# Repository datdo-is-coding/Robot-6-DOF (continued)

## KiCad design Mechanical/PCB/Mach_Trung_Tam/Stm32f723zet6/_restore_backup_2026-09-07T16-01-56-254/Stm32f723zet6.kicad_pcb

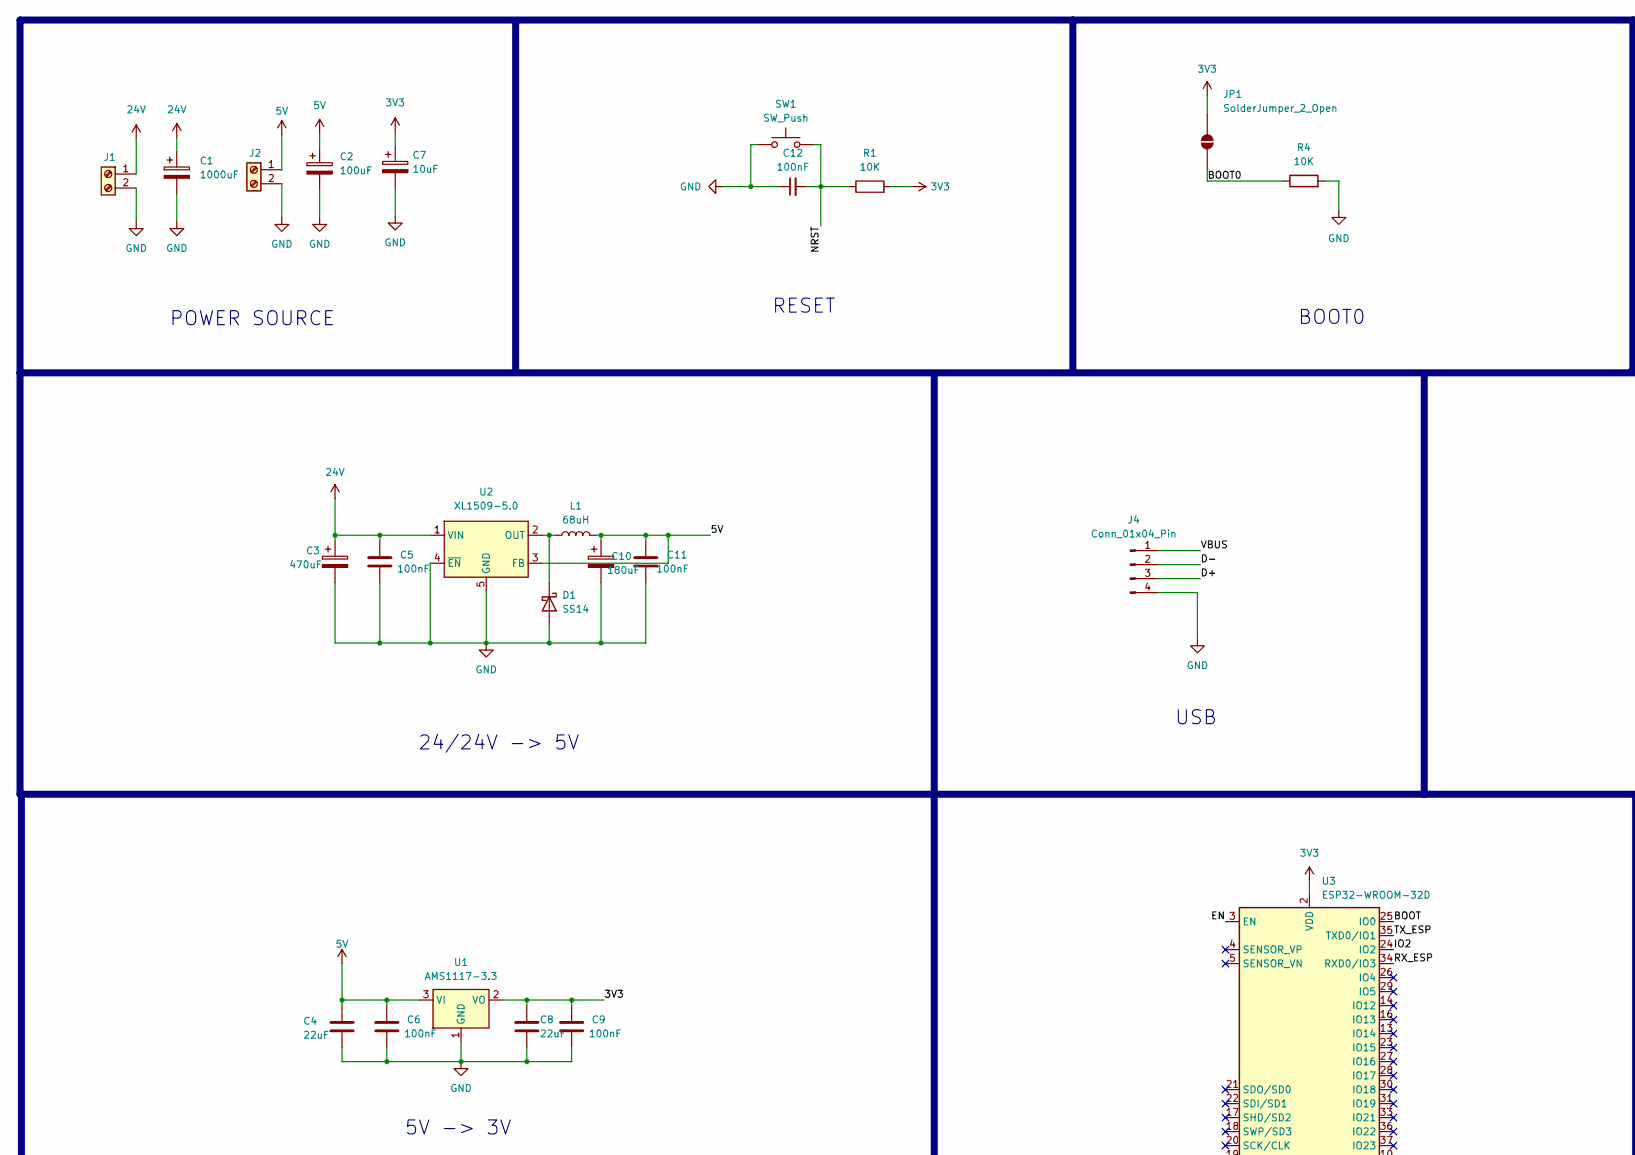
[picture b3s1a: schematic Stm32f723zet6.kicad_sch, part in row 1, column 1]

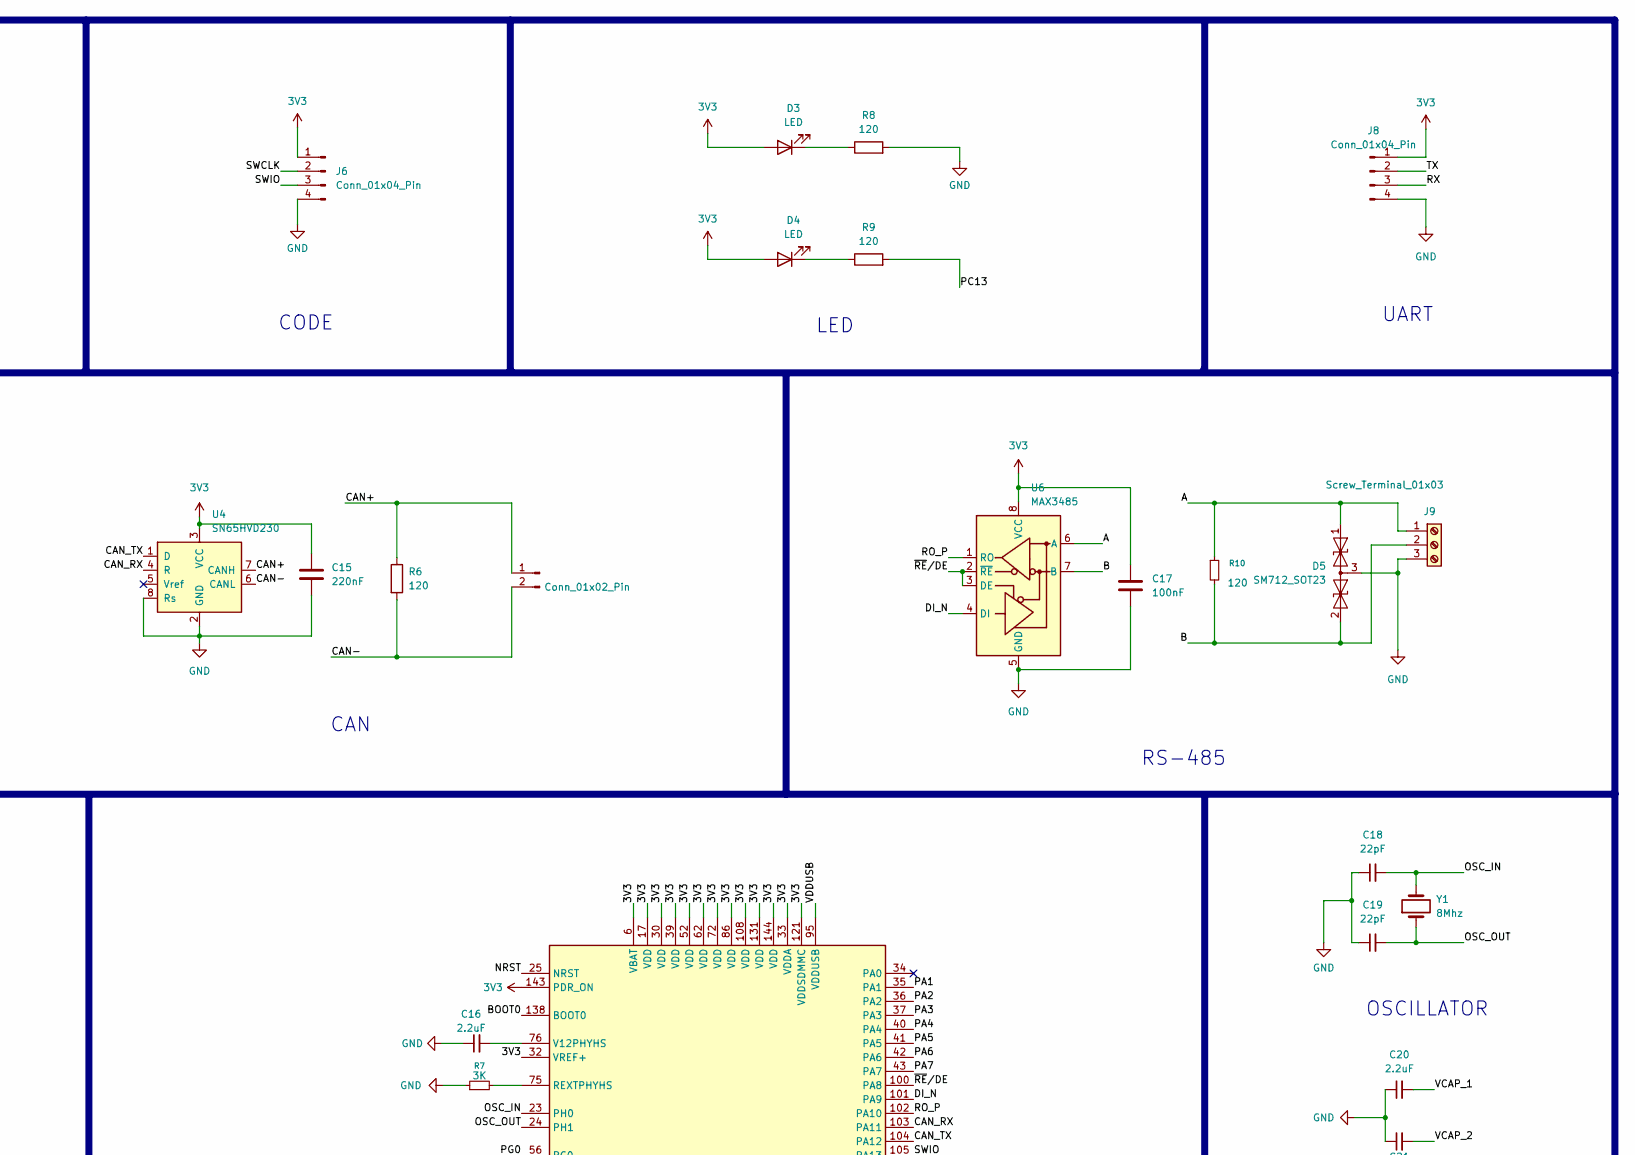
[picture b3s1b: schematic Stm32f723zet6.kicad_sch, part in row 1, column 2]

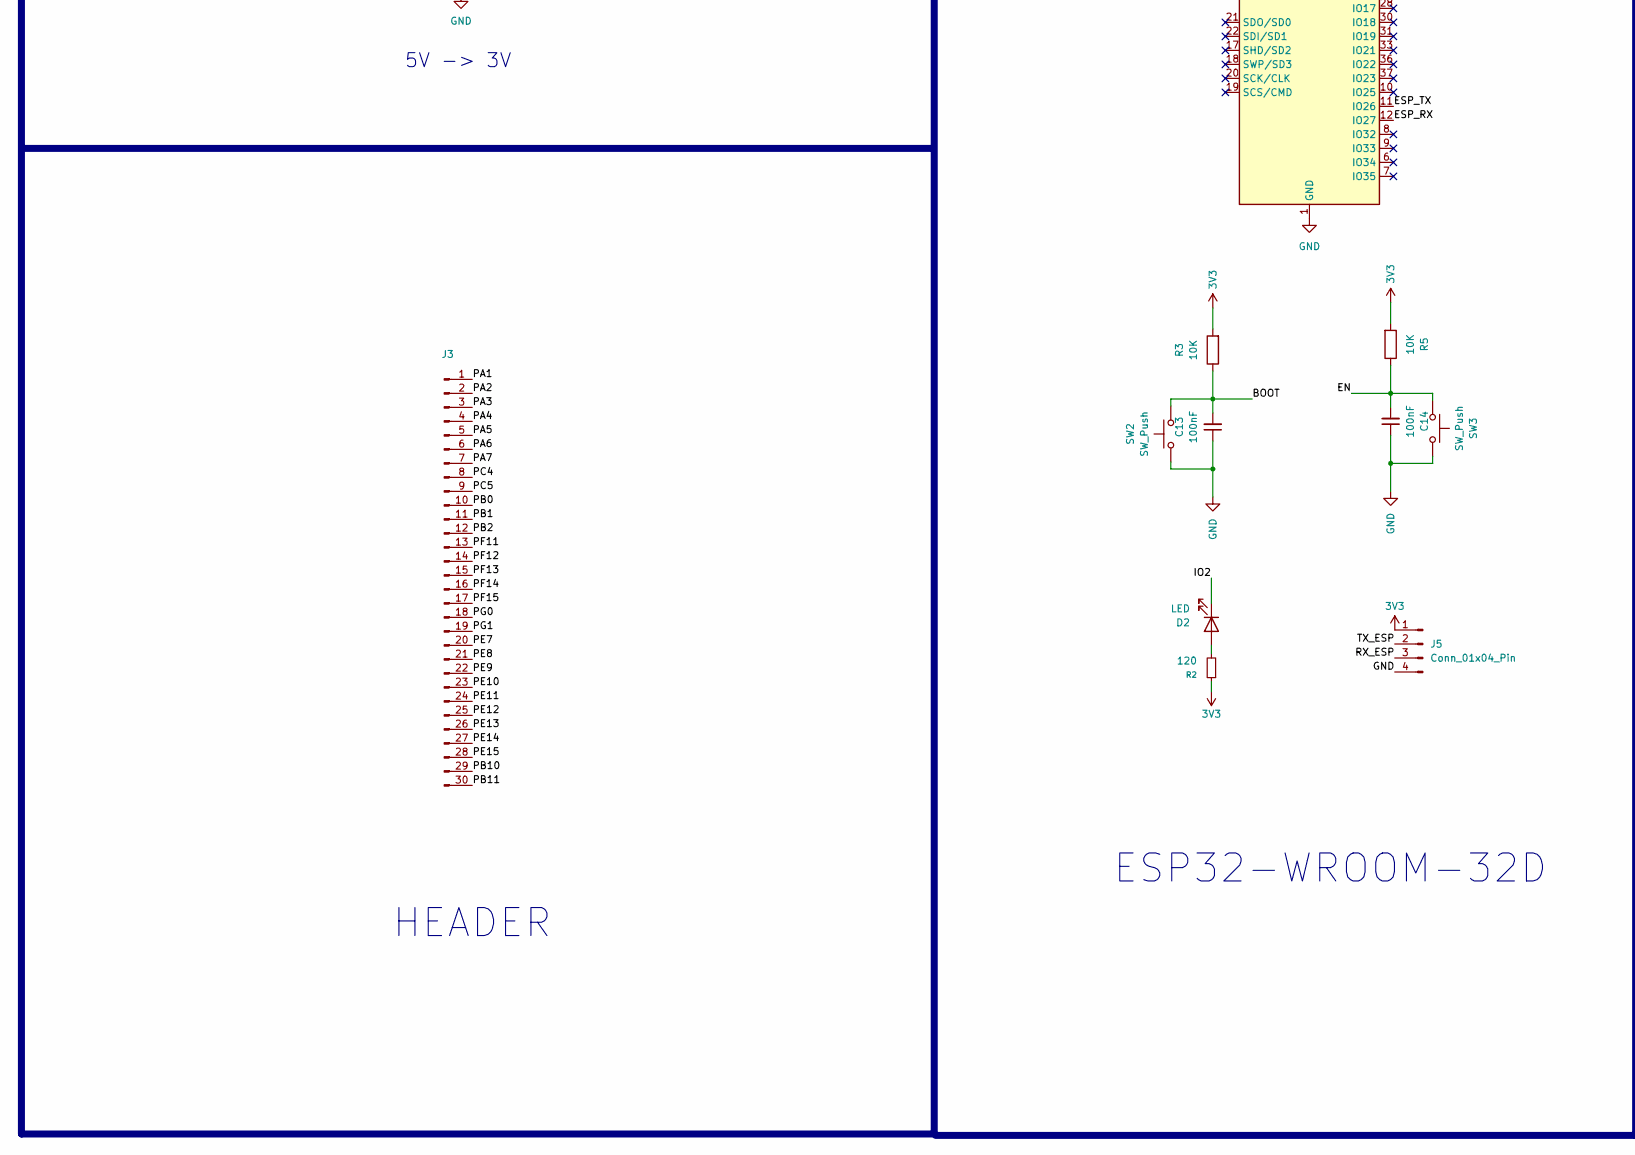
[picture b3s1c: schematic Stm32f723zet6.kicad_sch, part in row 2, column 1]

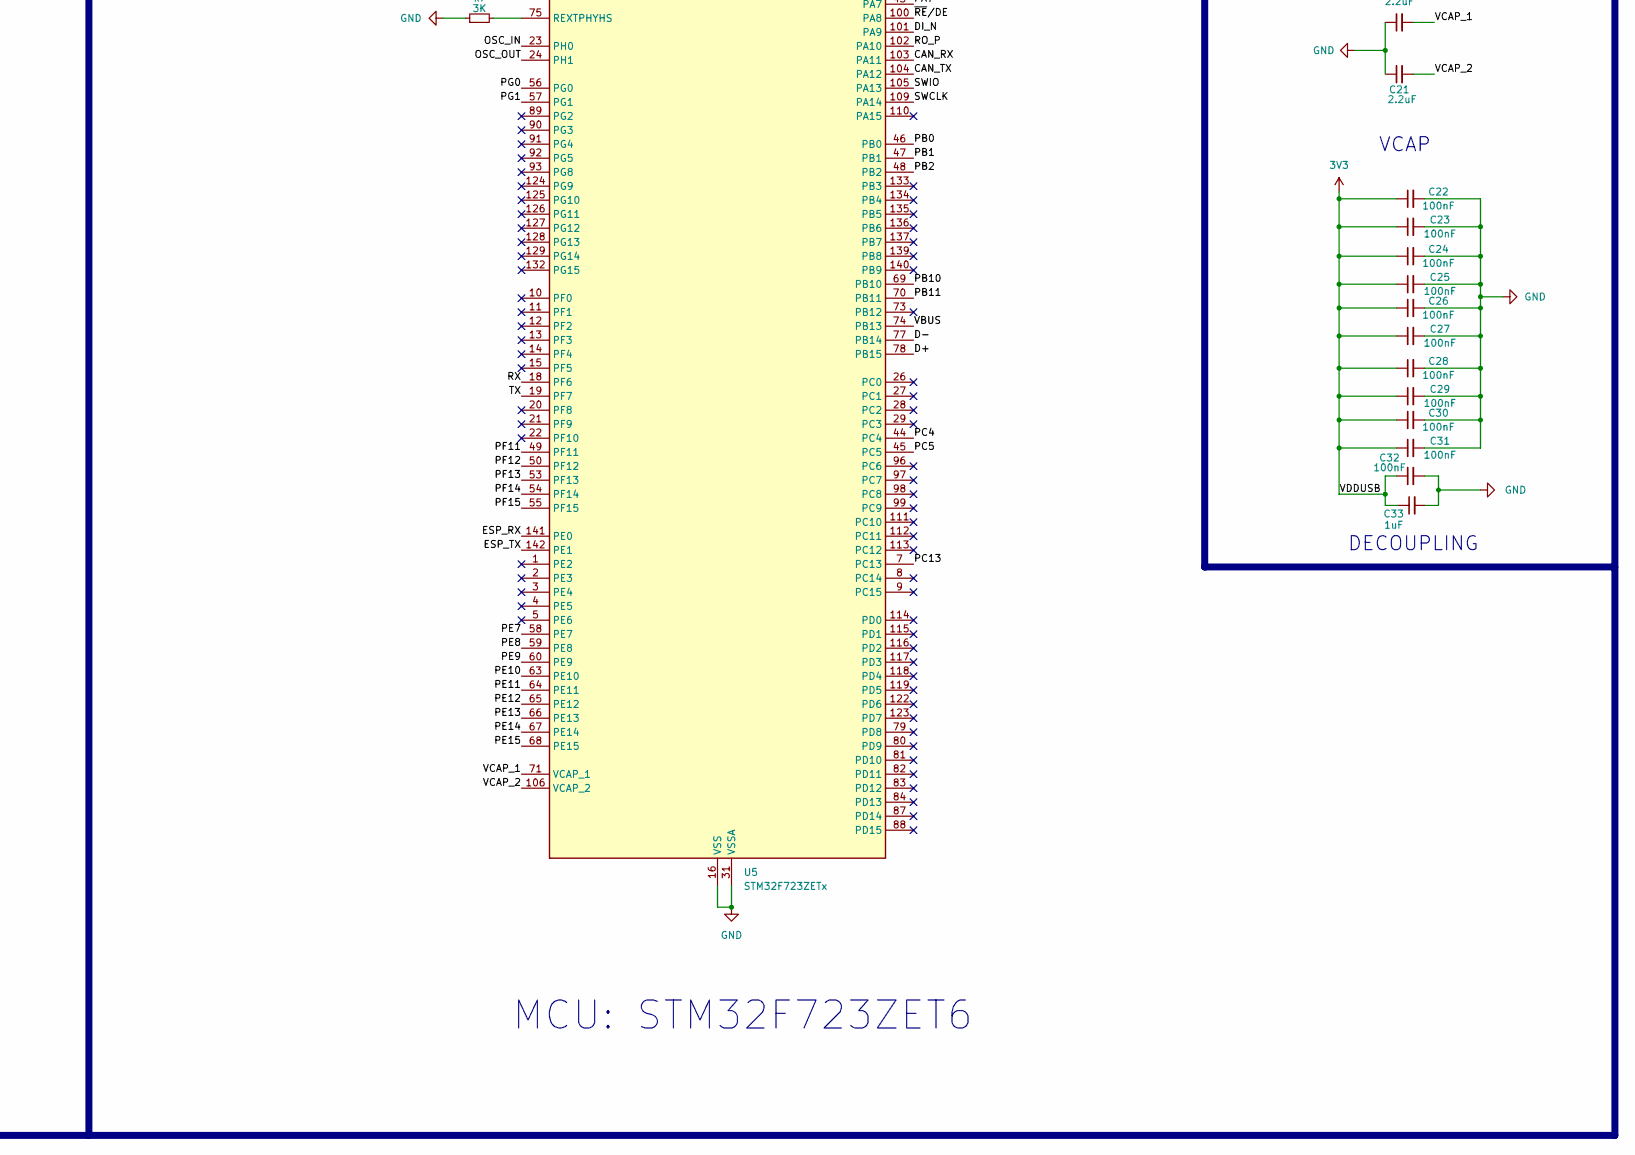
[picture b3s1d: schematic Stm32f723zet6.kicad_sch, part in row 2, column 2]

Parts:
C1: 1000uF; CP_Elec_10x10.5
C2: 100uF; CP_Elec_6.3x5.4
C3: 470uF; CP_Elec_8x10.5
C4, C8: 22uF; C_0805_2012Metric_Pad1.18x1.45mm_HandSolder
C5, C6, C9, C11, C12, C13, C14, C17, C22, C23, C24, C25, C26, C27, C28, C29, C30, C31, C32: 100nF; C_0805_2012Metric_Pad1.18x1.45mm_HandSolder
C7: 10uF; CP_Elec_4x5.4
C10: 180uF; CP_Elec_8x10
C15: 220nF; C_0805_2012Metric_Pad1.18x1.45mm_HandSolder
C16, C20, C21: 2.2uF; C_0805_2012Metric_Pad1.18x1.45mm_HandSolder
C18, C19: 22pF; C_0805_2012Metric_Pad1.18x1.45mm_HandSolder
C33: 1uF; C_0805_2012Metric_Pad1.18x1.45mm_HandSolder
D1: SS14; D_SMA
D2, D3, D4: LED; LED_0805_2012Metric_Pad1.15x1.40mm_HandSolder
D5: SM712_SOT23; SOT-23
J1: Screw_Terminal_01x02; TerminalBlock_Phoenix_MKDS-1,5-2-5.08_1x02_P5.08mm_Horizont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
J2: Screw_Terminal_01x02; TerminalBlock_Phoenix_PT-1,5-2-3.5-H_1x02_P3.50mm_Horizontal
J3: Conn_01x30_Pin; PinHeader_1x30_P2.54mm_Vertical
J4, J5, J6, J8: Conn_01x04_Pin; PinHeader_1x04_P2.54mm_Vertical
J7: Conn_01x02_Pin; PinHeader_1x02_P2.54mm_Vertical
J9: Screw_Terminal_01x03; TerminalBlock_Phoenix_PT-1,5-3-3.5-H_1x03_P3.50mm_Horizontal
JP1: SolderJumper_2_Open; SolderJumper-2_P1.3mm_Open_Pad1.0x1.5mm
L1: 68uH; L_0805_2012Metric_Pad1.05x1.20mm_HandSolder
R1, R3, R4, R5: 10K; R_0805_2012Metric_Pad1.20x1.40mm_HandSolder
R2, R6, R8, R9, R10: 120; R_0805_2012Metric_Pad1.20x1.40mm_HandSolder
R7: 3K; R_0805_2012Metric_Pad1.20x1.40mm_HandSolder
SW1, SW2, SW3: SW_Push; SW_Tactile_SPST_NO_Straight_CK_PTS636Sx25SMTRLFS
U1: AMS1117-3.3; SOT-223-3_TabPin2
U2: XL1509-5.0; SOIC-8_3.9x4.9mm_P1.27mm
U3: ESP32-WROOM-32D
U4: SN65HVD230; SOIC-8_3.9x4.9mm_P1.27mm
U5: STM32F723ZETx; LQFP-144_20x20mm_P0.5mm
U6: MAX3485; SOIC-8_3.9x4.9mm_P1.27mm
Y1: 8Mhz; Crystal_HC49-U_Vertical

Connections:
3V3: C7.1, C8.1, C9.1, C15.1, C17.2, C22.1, C23.1, C24.1, C25.1, C26.1, C27.1, C28.1, C29.1, C30.1, C31.1, C32.1, C33.1, D3.2 (A), D4.2 (A), J5.1, J6.1, J8.1, JP1.2 (B), R1.2, R2.1, R3.2, R5.2, U1.2 (VO), U3.2 (VDD), U4.3 (VCC), U5.6 (VBAT), U5.17 (VDD), U5.30 (VDD), U5.32 (VREF+), U5.33 (VDDA), U5.39 (VDD), U5.52 (VDD), U5.62 (VDD), U5.72 (VDD), U5.86 (VDD), U5.95 (VDDUSB), U5.108 (VDD), U5.121 (VDDSDMMC), U5.131 (VDD), U5.143 (PDR_ON), U5.144 (VDD), U6.8 (VCC)
5V: C2.1, C4.1, C6.1, C10.1, C11.1, J2.1, L1.2, U1.3 (VI), U2.3 (FB)
24V: C1.1, C3.1, C5.1, J1.1, U2.1 (VIN)
/A: D5.1 (A1), J9.1, R10.1, U6.6 (A)
/B: D5.2 (A2), J9.2, R10.2, U6.7 (B)
/BOOT: C13.2, R3.1, SW2.2, U3.25 (IO0)
/BOOT0: JP1.1 (A), R4.1, U5.138 (BOOT0)
/CAN+: J7.1, R6.1, U4.7 (CANH)
/CAN-: J7.2, R6.2, U4.6 (CANL)
/CAN_RX: U4.4 (R), U5.103 (PA11)
/CAN_TX: U4.1 (D), U5.104 (PA12)
/D+: J4.3, U5.78 (PB15)
/D-: J4.2, U5.77 (PB14)
/DI_N: U5.101 (PA9), U6.4 (DI)
/EN: C14.2, R5.1, SW3.2, U3.3 (EN)
/ESP_RX: U3.12 (IO27), U5.141 (PE0)
/ESP_TX: U3.11 (IO26), U5.142 (PE1)
/IO2: D2.1 (K), U3.24 (IO2)
/NRST: C12.2, R1.1, SW1.2, U5.25 (NRST)
/OSC_IN: C18.2, U5.23 (PH0), Y1.2
/OSC_OUT: C19.2, U5.24 (PH1), Y1.1
/PA1: J3.1, U5.35 (PA1)
/PA2: J3.2, U5.36 (PA2)
/PA3: J3.3, U5.37 (PA3)
/PA4: J3.4, U5.40 (PA4)
/PA5: J3.5, U5.41 (PA5)
/PA6: J3.6, U5.42 (PA6)
/PA7: J3.7, U5.43 (PA7)
/PB0: J3.10, U5.46 (PB0)
/PB1: J3.11, U5.47 (PB1)
/PB2: J3.12, U5.48 (PB2)
/PB10: J3.29, U5.69 (PB10)
/PB11: J3.30, U5.70 (PB11)
/PC4: J3.8, U5.44 (PC4)
/PC5: J3.9, U5.45 (PC5)
/PC13: R9.2, U5.7 (PC13)
/PE7: J3.20, U5.58 (PE7)
/PE8: J3.21, U5.59 (PE8)
/PE9: J3.22, U5.60 (PE9)
/PE10: J3.23, U5.63 (PE10)
/PE11: J3.24, U5.64 (PE11)
/PE12: J3.25, U5.65 (PE12)
/PE13: J3.26, U5.66 (PE13)
/PE14: J3.27, U5.67 (PE14)
/PE15: J3.28, U5.68 (PE15)
/PF11: J3.13, U5.49 (PF11)
/PF12: J3.14, U5.50 (PF12)
/PF13: J3.15, U5.53 (PF13)
/PF14: J3.16, U5.54 (PF14)
/PF15: J3.17, U5.55 (PF15)
/PG0: J3.18, U5.56 (PG0)
/PG1: J3.19, U5.57 (PG1)
/RO_P: U5.102 (PA10), U6.1 (RO)
/RX: J8.3, U5.18 (PF6)
/RX_ESP: J5.3, U3.34 (RXD0/IO3)
/SWCLK: J6.2, U5.109 (PA14)
/SWIO: J6.3, U5.105 (PA13)
/TX: J8.2, U5.19 (PF7)
/TX_ESP: J5.2, U3.35 (TXD0/IO1)
/VBUS: J4.1, U5.74 (PB13)
/VCAP_1: C20.2, U5.71 (VCAP_1)
/VCAP_2: C21.2, U5.106 (VCAP_2)
/~RE/DE: U5.100 (PA8), U6.2 (~RE), U6.3 (DE)
GND: C1.2, C2.2, C3.2, C4.2, C5.2, C6.2, C7.2, C8.2, C9.2, C10.2, C11.2, C12.1, C13.1, C14.1, C15.2, C16.1, C17.1, C18.1, C19.1, C20.1, C21.1, C22.2, C23.2, C24.2, C25.2, C26.2, C27.2, C28.2, C29.2, C30.2, C31.2, C32.2, C33.2, D1.2 (A), D5.3 (common), J1.2, J2.2, J4.4, J5.4, J6.4, J8.4, J9.3, R4.2, R7.1, R8.2, SW1.1, SW2.1, SW3.1, U1.1 (GND), U2.4 (~EN), U2.5 (GND), U2.6 (GND), U2.7 (GND), U2.8 (GND), U3.1 (GND), U3.15 (GND), U3.38 (GND), U3.39 (GND), U4.2 (GND), U4.8 (Rs), U5.16 (VSS), U5.31 (VSSA), U5.38 (VSS), U5.51 (VSS), U5.61 (VSS), U5.85 (VSS), U5.94 (VSS), U5.107 (VSS), U5.120 (VSS), U5.130 (VSS), U6.5 (GND)
unnamed: D1.1 (K), L1.1, U2.2 (OUT)
unnamed: D2.2 (A), R2.2
unnamed: D3.1 (K), R8.1
unnamed: D4.1 (K), R9.1
unnamed: R7.2, U5.75 (REXTPHYHS)
unnamed: C16.2, U5.76 (V12PHYHS)

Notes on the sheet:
5V -> 3V
VCAP
CODE
HEADER
POWER SOURCE
RESET
BOOT0
CAN
USB
MCU: STM32F723ZET6
24/24V -> 5V
LED
UART
OSCILLATOR
DECOUPLING
ESP32-WROOM-32D
RS-485

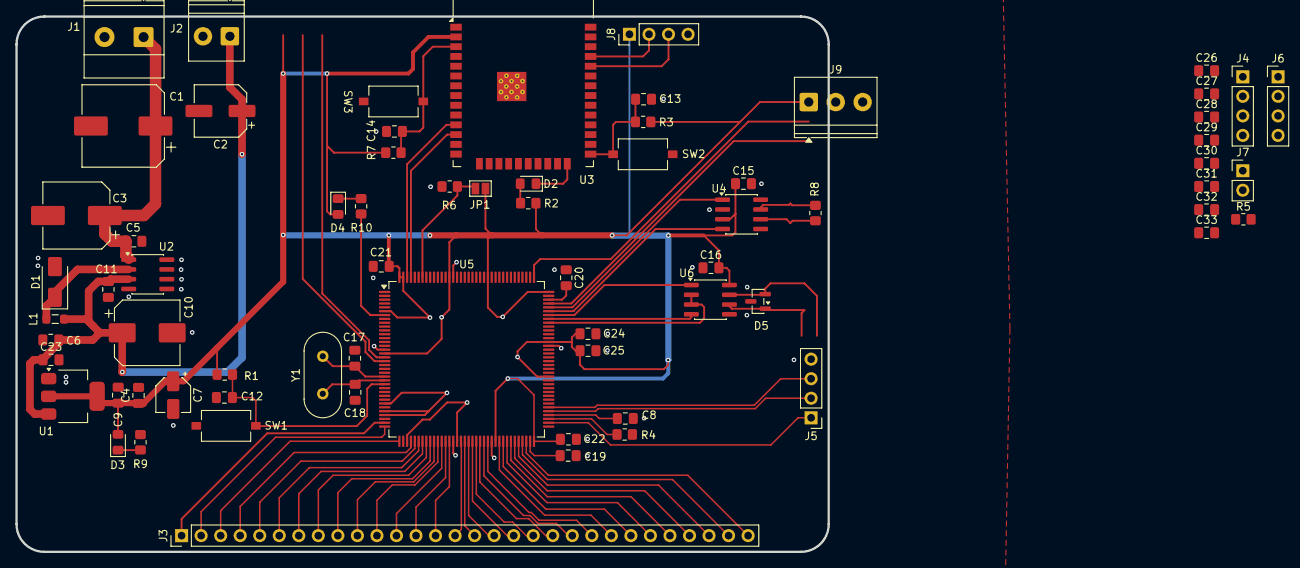
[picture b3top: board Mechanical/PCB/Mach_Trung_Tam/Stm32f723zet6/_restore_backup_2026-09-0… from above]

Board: 2 copper layers, 105.6 x 69.6 mm, 69 parts (0 on the bottom side), 70 nets.

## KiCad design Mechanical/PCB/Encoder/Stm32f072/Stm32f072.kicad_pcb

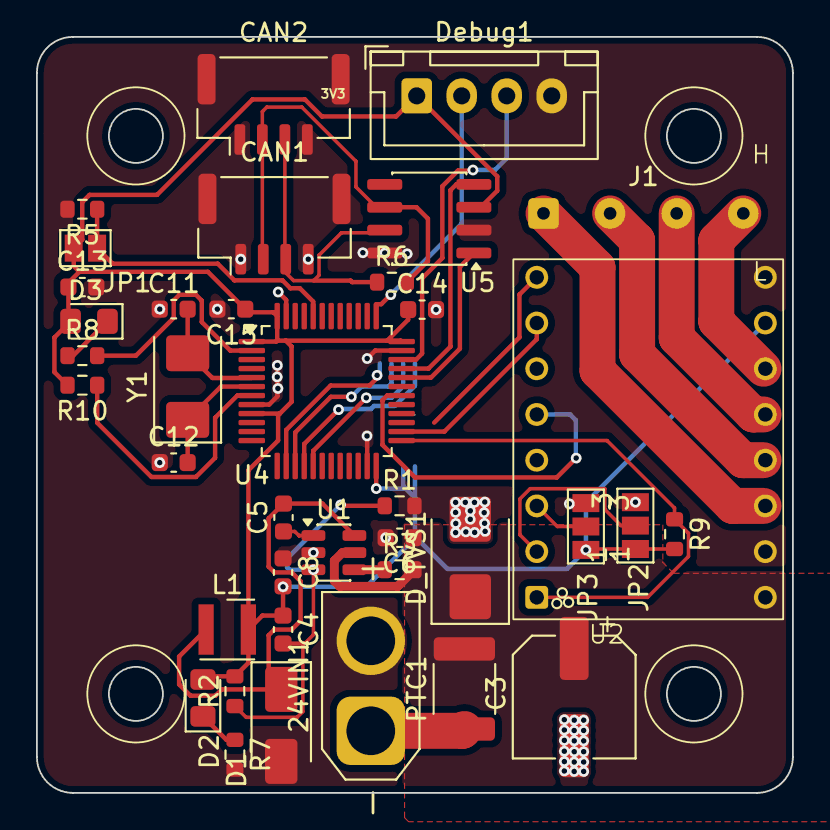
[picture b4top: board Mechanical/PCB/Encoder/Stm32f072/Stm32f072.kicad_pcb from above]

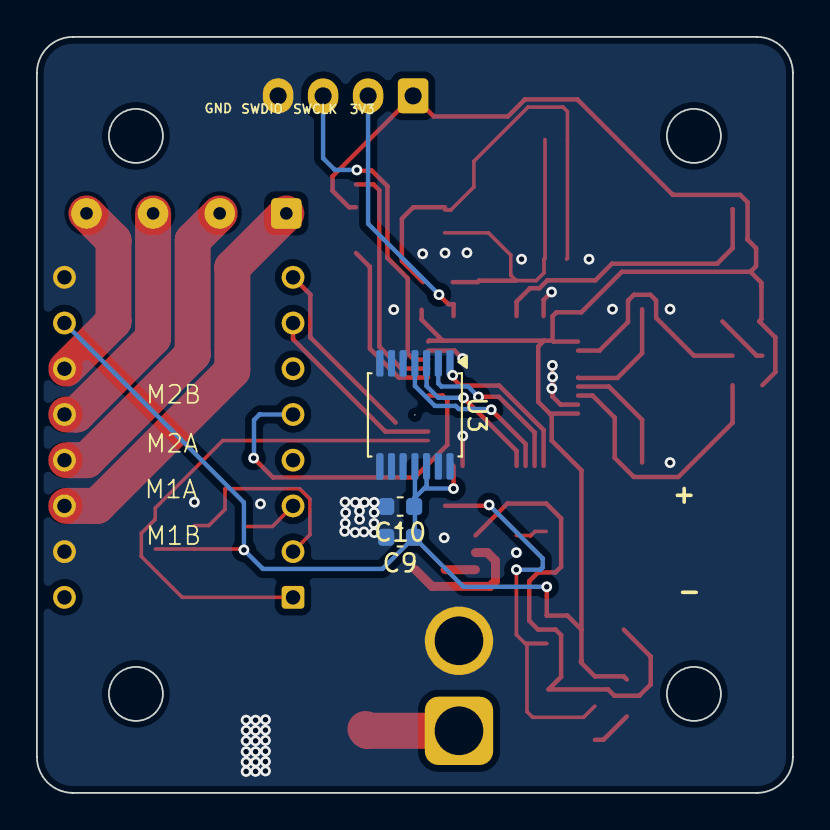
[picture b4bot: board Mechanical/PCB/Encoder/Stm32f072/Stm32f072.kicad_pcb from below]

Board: 2 copper layers, 42.0 x 42.0 mm, 41 parts (3 on the bottom side), 35 nets.

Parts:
24VIN1: Screw_Terminal_01x02; AMASS_XT30U-M_1x02_P5.0mm_Vertical
C3: 470uF; CP_Elec_6.3x7.7
C4: 33pF; C_0603_1608Metric
C5, C9, C14, C15: 100nF; C_0603_1608Metric
C6: 4.7uF; C_0603_1608Metric
C8: 10uF; C_0603_1608Metric
C10: 1uF; C_0603_1608Metric
C11, C12: 22pF; C_0603_1608Metric
C13: 220nF; C_0603_1608Metric
CAN1, CAN2: CAN; JST_GH_BM04B-GHS-TBT_1x04-1MP_P1.25mm_Vertical
D1: SS16; D_SMA
D2, D3: LED; LED_0805_2012Metric_Pad1.15x1.40mm_HandSolder
D_TVS1: SMBJ26A; D_SMB
Debug1: Conn_01x04_Pin; JST_XH_B4B-XH-A_1x04_P2.50mm_Vertical
J1: Conn_01x04_Pin; SolderWire-0.127sqmm_1x04_P3.7mm_D0.48mm_OD1mm
JP1: SolderJumper_2_Open; SolderJumper-2_P1.3mm_Open_Pad1.0x1.5mm
JP2, JP3: SolderJumper_3_Open; SolderJumper-3_P1.3mm_Open_Pad1.0x1.5mm_NumberLabels
L1: 2.2uH; L_Wurth_WE-LQSH-3012
PTC1: Cau chi; R_1812_4532Metric_Pad1.30x3.40mm_HandSolder
R1: 40.2K; R_0603_1608Metric
R2: 124K; R_0603_1608Metric
R3: 220K; R_0603_1608Metric
R5, R9, R10: 10K; R_0603_1608Metric
R6: 120; R_0603_1608Metric
R7, R8: 470; R_0603_1608Metric
U1: MP2451DT-LF-Z; SOT-23-6
U2: Tmc2209 module
U3: AS5047D; TSSOP-14_4.4x5mm_P0.65mm
U4: STM32F072C8Tx; LQFP-48_7x7mm_P0.5mm
U5: SN65HVD230; SOIC-8_3.9x4.9mm_P1.27mm
Y1: Crystal; Crystal_SMD_5032-2Pin_5.0x3.2mm

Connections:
3V3: C4.1, C8.2, C9.1, C10.1, C13.1, C14.1, C15.1, D2.2 (A), D3.2 (A), Debug1.1, JP1.2 (B), JP2.1 (A), JP3.1 (A), L1.2, R2.2, R9.2, R10.2, U2.15 (VIO), U3.11 (VDD), U3.12 (VDD3V3), U4.1 (VBAT), U4.9 (VDDA), U4.24 (VDD), U4.36 (VDDIO2), U4.48 (VDD), U5.3 (VCC)
24V: C3.1, C6.1, D_TVS1.1 (K), PTC1.2, R3.2, U1.5 (VIN), U2.9 (VM)
/BOOT0: JP1.1 (A), R5.1, U4.44 (BOOT0)
/CANH: CAN1.3, CAN2.3, R6.1, U5.7 (CANH)
/CANL: CAN1.2, CAN2.2, R6.2, U5.6 (CANL)
/CAN_RX: U4.33 (PA12), U5.4 (R)
/CAN_TX: U4.32 (PA11), U5.1 (D)
/CLK: U3.2 (CLK), U4.15 (PA5)
/CS: U3.1 (~CS), U4.14 (PA4)
/DIR: U2.8 (DIR), U4.27 (PB14)
/EN: R9.1, U2.1 (EN), U4.25 (PB12)
/M1A: J1.2, U2.12 (M1A)
/M1B: J1.1, U2.11 (M1B)
/M2A: J1.3, U2.13 (M2A)
/M2B: J1.4, U2.14 (M2B)
/MISO: U3.3 (MISO), U4.17 (PA7)
/MOSI: U3.4 (MOSI), U4.16 (PA6)
/MS1: JP2.2 (C), U2.2 (MS1)
/MS2: JP3.2 (C), U2.3 (MS2)
/NRST: R10.1, U4.7 (NRST)
/OSC_IN: C11.2, U4.5 (PF0), Y1.2
/OSC_OUT: C12.2, U4.6 (PF1), Y1.1
/PA9: U2.5 (USART), U4.30 (PA9)
/PB13: U2.7 (STEP), U4.26 (PB13)
/PC13: R8.2, U4.2 (PC13)
/SWCLK: Debug1.2, U4.37 (PA14)
/SWDIO: Debug1.3, U4.34 (PA13)
GND: 24VIN1.2, C3.2, C6.2, C8.1, C9.2, C10.2, C11.1, C12.1, C13.2, C14.2, C15.2, CAN1.1, CAN1.4, CAN2.1, CAN2.4, D1.2 (A), D_TVS1.2 (A), Debug1.4, JP2.3 (B), JP3.3 (B), R1.2, R5.2, R7.2, U1.2 (GND), U2.10 (GND), U2.16 (GND), U3.5 (TST), U3.13 (GND), U4.8 (VSSA), U4.23 (VSS), U4.35 (VSS), U4.47 (VSS), U5.2 (GND), U5.8 (Rs)
unnamed: 24VIN1.1, PTC1.1
unnamed: C5.2, D1.1 (K), L1.1, U1.6 (SW)
unnamed: D2.1 (K), R7.1
unnamed: D3.1 (K), R8.1
unnamed: C5.1, U1.1 (BST)
unnamed: R3.1, U1.4 (EN)
unnamed: C4.2, R1.1, R2.1, U1.3 (FB)

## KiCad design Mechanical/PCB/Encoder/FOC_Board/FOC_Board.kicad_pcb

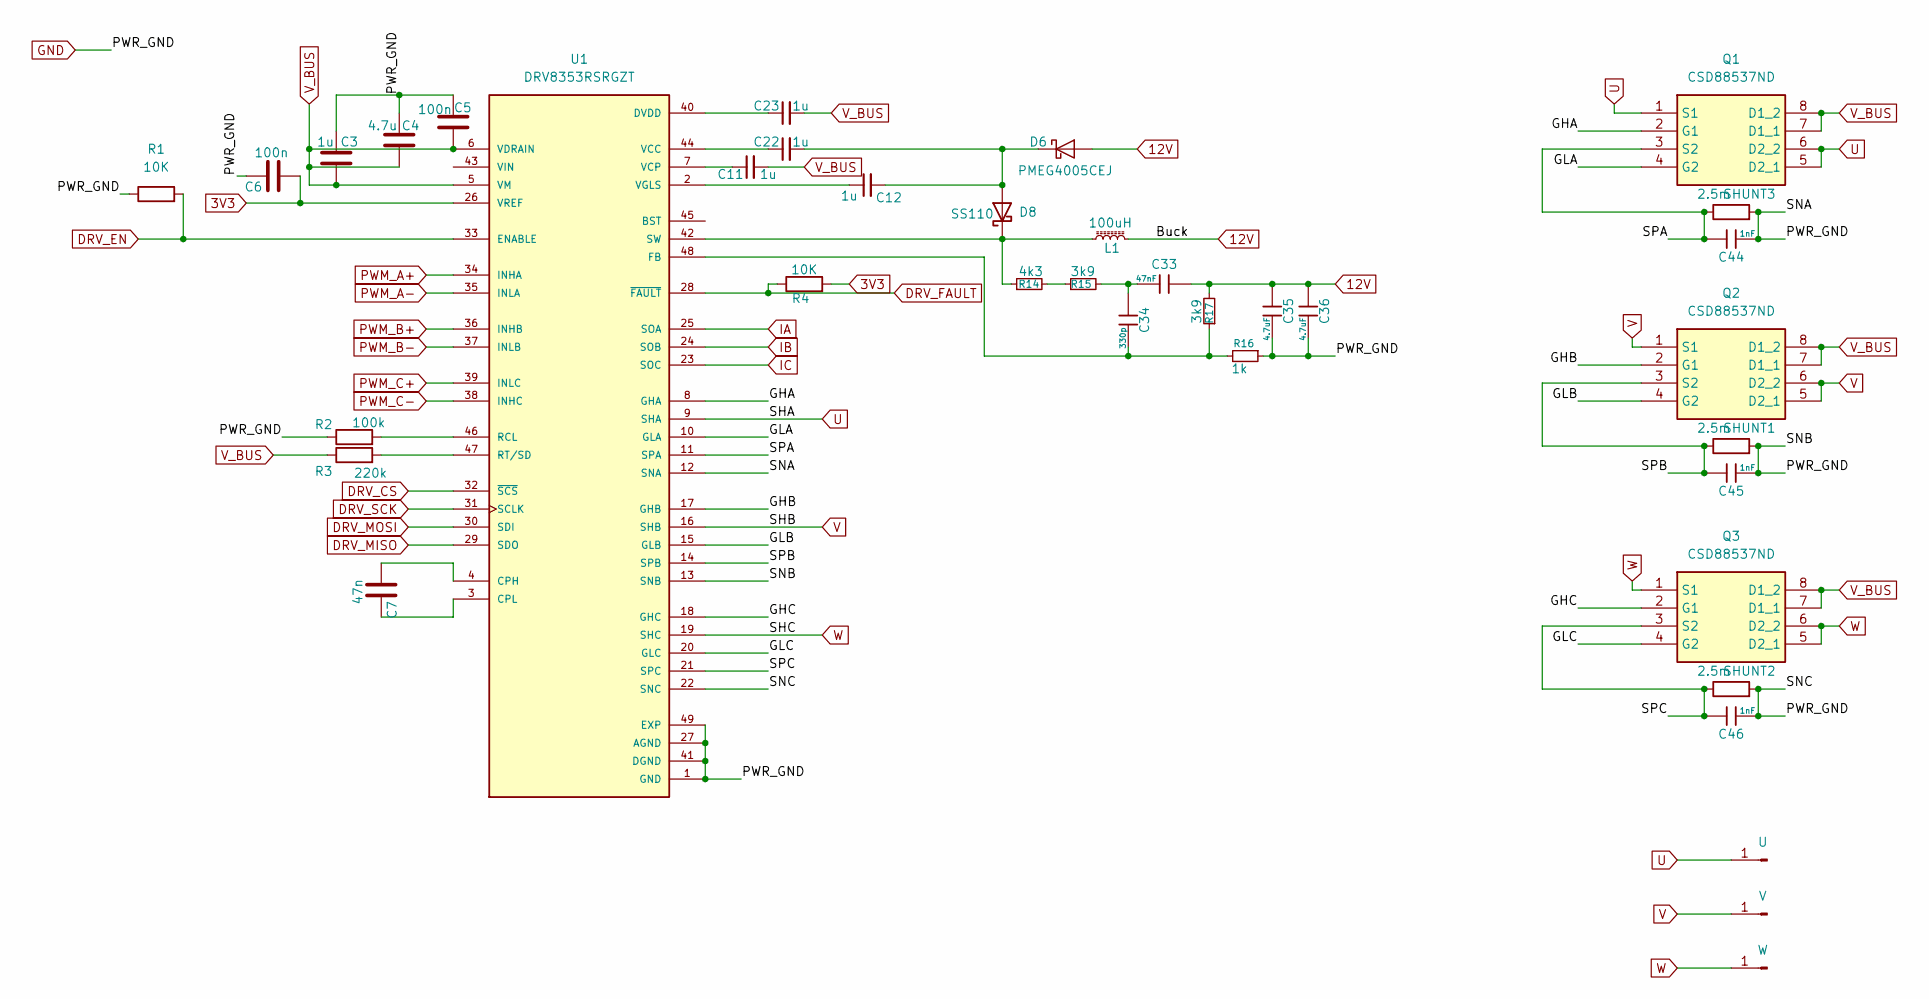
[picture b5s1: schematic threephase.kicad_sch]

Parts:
C3: 1u; C_1206_3216Metric
C4: 4.7u; C_1206_3216Metric
C5: 100n; C_1206_3216Metric
C6: 100n; C_0402_1005Metric
C7: 47n; C_1206_3216Metric
C11, C12, C22, C23: 1u; C_0402_1005Metric
C33: 47nF; C_0805_2012Metric; Voltage Rated 25V; Tolerance ±10%; Part CL21A106KAYNNNE; LCSC C15850
C34: 330p; C_0805_2012Metric; Voltage Rated 25V; Tolerance ±10%; Part CL21A106KAYNNNE; LCSC C15850
C35, C36: 4.7uF; C_0805_2012Metric; Voltage Rated 25V; Tolerance ±10%; Part CL21A106KAYNNNE; LCSC C15850
C44, C45, C46: 1nF; C_0805_2012Metric; Voltage Rated 25V; Tolerance ±10%; Part CL21A106KAYNNNE; LCSC C15850
D6: PMEG4005CEJ; D_SOD-323F
D8: SS110; D_SMA
J4: U; SolderWire-1.5sqmm_1x01_D1.7mm_OD3mm
J5: V; SolderWire-1.5sqmm_1x01_D1.7mm_OD3mm
J6: W; SolderWire-1.5sqmm_1x01_D1.7mm_OD3mm
L1: 100uH; L_Cenker_CKCS8040
Q1, Q2, Q3: CSD88537ND; SOIC127P600X175-8N; Manufacturer_Part_Number CSD88537ND; Mouser Part Number 595-CSD88537ND
R1, R4: 10K; R_0402_1005Metric
R2: 100k; R_0603_1608Metric
R3: 220k; R_0603_1608Metric
R14: 4k3; R_0805_2012Metric
R15, R17: 3k9; R_0805_2012Metric
R16: 1k; R_0805_2012Metric
SHUNT1, SHUNT2, SHUNT3: 2.5m; R_2512_6332Metric
U1: DRV8353RSRGZT; QFN50P700X700X100-49N; PARTREV A

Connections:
12V: C33.2, C35.2, C36.2, D6.2 (A), L1.2, R17.2; also elsewhere on the board
/Three_phase/GHA: Q1.2 (G1), U1.8 (GHA)
/Three_phase/GHB: Q2.2 (G1), U1.17 (GHB)
/Three_phase/GHC: Q3.2 (G1), U1.18 (GHC)
/Three_phase/GLA: Q1.4 (G2), U1.10 (GLA)
/Three_phase/GLB: Q2.4 (G2), U1.15 (GLB)
/Three_phase/GLC: Q3.4 (G2), U1.20 (GLC)
/Three_phase/SPA: C44.2, Q1.3 (S2), SHUNT3.1, U1.11 (SPA)
/Three_phase/SPB: C45.2, Q2.3 (S2), SHUNT1.1, U1.14 (SPB)
/Three_phase/SPC: C46.2, Q3.3 (S2), SHUNT2.1, U1.21 (SPC)
DRV_CS: U1.32 (~SCS); also elsewhere on the board
DRV_EN: R1.2, U1.33 (ENABLE); also elsewhere on the board
DRV_FAULT: R4.1, U1.28 (~FAULT); also elsewhere on the board
DRV_MISO: U1.29 (SDO); also elsewhere on the board
DRV_MOSI: U1.30 (SDI); also elsewhere on the board
DRV_SCK: U1.31 (SCLK); also elsewhere on the board
GND: C3.1, C4.1, C5.1, C6.1, C35.1, C36.1, C44.1, C45.1, C46.1, R1.1, R2.1, R16.1, SHUNT1.2, SHUNT2.2, SHUNT3.2, U1.1 (GND), U1.12 (SNA), U1.13 (SNB), U1.22 (SNC), U1.27 (AGND), U1.41 (DGND), U1.49 (EXP); also elsewhere on the board
IA: U1.25 (SOA); also elsewhere on the board
IB: U1.24 (SOB); also elsewhere on the board
IC: U1.23 (SOC); also elsewhere on the board
unnamed: C33.1, C34.2, R15.2
unnamed: C12.2, C22.2, D6.1 (K), D8.2 (A)
unnamed: D8.1 (K), L1.1, R14.1, U1.42 (SW)
unnamed: R14.2, R15.1
unnamed: C7.2, U1.4 (CPH)
unnamed: C7.1, U1.3 (CPL)
unnamed: C23.1, U1.40 (DVDD)
unnamed: C34.1, R16.2, R17.1, U1.48 (FB)
unnamed: R2.2, U1.46 (RCL)
unnamed: R3.2, U1.47 (RT/SD)
unnamed: C22.1, U1.44 (VCC)
unnamed: C11.1, U1.7 (VCP)
unnamed: C12.1, U1.2 (VGLS)
PWM_A+: U1.34 (INHA); also elsewhere on the board
PWM_A-: U1.35 (INLA); also elsewhere on the board
PWM_B+: U1.36 (INHB); also elsewhere on the board
PWM_B-: U1.37 (INLB); also elsewhere on the board
PWM_C+: U1.39 (INLC); also elsewhere on the board
PWM_C-: U1.38 (INHC); also elsewhere on the board
U: J4.1 (Pin_1_1), Q1.1 (S1), Q1.5 (D2_1), Q1.6 (D2_2), U1.9 (SHA)
V: J5.1 (Pin_1_1), Q2.1 (S1), Q2.5 (D2_1), Q2.6 (D2_2), U1.16 (SHB)
V_BUS: C3.2, C4.2, C5.2, C11.2, C23.2, Q1.7 (D1_1), Q1.8 (D1_2), Q2.7 (D1_1), Q2.8 (D1_2), Q3.7 (D1_1), Q3.8 (D1_2), R3.1, U1.5 (VM), U1.6 (VDRAIN), U1.43 (VIN); also elsewhere on the board
W: J6.1 (Pin_1_1), Q3.1 (S1), Q3.5 (D2_1), Q3.6 (D2_2), U1.19 (SHC)

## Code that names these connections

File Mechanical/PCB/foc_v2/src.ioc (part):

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Mcu.Name=STM32F405RGTx
Mcu.Package=LQFP64
Mcu.UserName=STM32F405RGTx
PA10.Signal=S_TIM1_CH3
PA11.Mode=Device_Only
PA11.Signal=USB_OTG_FS_DM
PA12.Mode=Device_Only
PA12.Signal=USB_OTG_FS_DP
PA13.Mode=Serial_Wire
PA13.Signal=SYS_JTMS-SWDIO
PA14.Mode=Serial_Wire
PA14.Signal=SYS_JTCK-SWCLK
PA3.Signal=ADCx_IN3
PA4.Signal=ADCx_IN4
PA5.Mode=Full_Duplex_Master
PA5.Signal=SPI1_SCK
PA6.Signal=ADCx_IN6
PA8.Signal=S_TIM1_CH1
PA9.Signal=S_TIM1_CH2
PB11.GPIOParameters=GPIO_Label
PB11.GPIO_Label=NFAULT1
PB11.Signal=GPIO_Input
PB13.Mode=PWM Generation1 CH1 CH1N
PB13.Signal=TIM1_CH1N
PB14.Mode=PWM Generation2 CH2 CH2N
PB14.Signal=TIM1_CH2N
PB15.Mode=PWM Generation3 CH3 CH3N
PB15.Signal=TIM1_CH3N
PB4.Mode=Full_Duplex_Master
PB4.Signal=SPI1_MISO
PB5.Mode=Full_Duplex_Master
PB5.Signal=SPI1_MOSI
PB8.GPIOParameters=GPIO_PuPd
PB8.GPIO_PuPd=GPIO_PULLUP
PB8.Mode=CAN_Activate
PB8.Signal=CAN1_RX
PB9.Mode=CAN_Activate
PB9.Signal=CAN1_TX
PC10.GPIOParameters=PinState,GPIO_Label
PC10.GPIO_Label=SPI_CS
PC10.Signal=GPIO_Output
PC13-ANTI_TAMP.GPIOParameters=GPIO_Label
PC13-ANTI_TAMP.GPIO_Label=LED_R
PC13-ANTI_TAMP.Signal=GPIO_Output
PC14-OSC32_IN.GPIOParameters=GPIO_Label
PC14-OSC32_IN.GPIO_Label=LED_G
PC14-OSC32_IN.Signal=GPIO_Output
PA1.Signal=ADCx_IN1
PC4.GPIOParameters=GPIO_Label
PC4.GPIO_Label=CSA_CAL1
PC4.Signal=GPIO_Output
PC9.GPIOParameters=GPIO_Label
PC9.GPIO_Label=EN_GATE1
PC9.Signal=GPIO_Output
PH0-OSC_IN.Mode=HSE-External-Oscillator
PH0-OSC_IN.Signal=RCC_OSC_IN
PH1-OSC_OUT.Mode=HSE-External-Oscillator
PH1-OSC_OUT.Signal=RCC_OSC_OUT
RCC.HSE_VALUE=12000000
RCC.SYSCLKFreq_VALUE=168000000
RCC.SYSCLKSource=RCC_SYSCLKSOURCE_PLLCLK
board=custom
PB3.Signal=SPI3_SCK
PC11.Signal=SPI3_MISO
PC12.Signal=SPI3_MOSI
PA15.Signal=GPIO_Output
PA15.GPIO_Label=HALL_CS
PB3.Mode=Full_Duplex_Master
PA15.GPIOParameters=PinState,GPIO_PuPd,GPIO_Label
PA15.PinState=GPIO_PIN_SET
PA15.GPIO_PuPd=GPIO_PULLUP
PC10.PinState=GPIO_PIN_SET
PC11.Mode=Full_Duplex_Master
PC12.Mode=Full_Duplex_Master
PA0-WKUP.Signal=GPIO_Input
PA0-WKUP.GPIOParameters=GPIO_Label
PA0-WKUP.GPIO_Label=USB_VBUS
PB10.Signal=SPI2_SCK
PB10.Mode=Full_Duplex_Master
PC2.Signal=SPI2_MISO
PC2.Mode=Full_Duplex_Master
PC3.Signal=SPI2_MOSI
PC3.Mode=Full_Duplex_Master
PB12.Signal=GPIO_Output
PB12.GPIOParameters=PinState,GPIO_PuPd,GPIO_Label
PB12.PinState=GPIO_PIN_SET
PB12.GPIO_PuPd=GPIO_PULLUP
PB12.GPIO_Label=ENC2_CS

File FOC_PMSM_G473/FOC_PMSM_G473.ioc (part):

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Mcu.Name=STM32G473R(B-C-E)Tx
Mcu.Package=LQFP64
Mcu.UserName=STM32G473RETx
PA0.GPIOParameters=GPIO_Label
PA0.GPIO_Label=FET_TEMP
PA0.Mode=IN1-Single-Ended
PA0.Signal=ADC1_IN1
PA10.Signal=S_TIM1_CH3
PA11.Mode=Device
PA11.Signal=USB_DM
PA12.Mode=Device
PA12.Signal=USB_DP
PA13.Mode=Serial_Wire
PA13.Signal=SYS_JTMS-SWDIO
PA14.Mode=Serial_Wire
PA14.Signal=SYS_JTCK-SWCLK
PA15.Signal=S_TIM2_CH1
PA3.GPIOParameters=GPIO_Label
PA3.GPIO_Label=VSENSE_A
PA3.Mode=IN4-Single-Ended
PA3.Signal=ADC1_IN4
PA5.GPIOParameters=GPIO_Label
PA5.GPIO_Label=DRV_SCK
PA5.Mode=Full_Duplex_Master
PA5.Signal=SPI1_SCK
PA6.GPIOParameters=GPIO_Label
PA6.GPIO_Label=DRV_MISO
PA6.Mode=Full_Duplex_Master
PA6.Signal=SPI1_MISO
PA7.Signal=SharedAnalog_PA7
PA8.Signal=S_TIM1_CH1
PA9.Signal=S_TIM1_CH2
PB0.Mode=PWM Generation2 CH2 CH2N
PB0.Signal=TIM1_CH2N
PB1.Signal=SharedAnalog_PB1
PB10.GPIOParameters=GPIO_Label
PB10.GPIO_Label=DRV_BKIN
PB10.Mode=Activate-Break-Input
PB10.Signal=TIM1_BKIN
PB12.GPIOParameters=GPIO_Label
PB12.GPIO_Label=CAN_RX
PB12.Mode=FDCAN_Activate
PB12.Signal=FDCAN2_RX
PB13.GPIOParameters=GPIO_Label
PB13.GPIO_Label=CAN_TX
PB13.Mode=FDCAN_Activate
PB13.Signal=FDCAN2_TX
PB14.GPIOParameters=GPIO_Label
PB14.GPIO_Label=VSENSE_B
PB14.Mode=IN5-Single-Ended
PB14.Signal=ADC1_IN5
PB15.Mode=PWM Generation3 CH3 CH3N
PB15.Signal=TIM1_CH3N
PB5.GPIOParameters=GPIO_Label
PB5.GPIO_Label=DRV_MOSI
PB5.Mode=Full_Duplex_Master
PB5.Signal=SPI1_MOSI
PB6.GPIOParameters=GPIO_Label
PB6.GPIO_Label=ENC_EN
PB6.Signal=GPIO_Output
PB7.GPIOParameters=GPIO_Speed,PinState,GPIO_Label
PB7.GPIO_Label=ENC_CS
PB7.GPIO_Speed=GPIO_SPEED_FREQ_HIGH
PB7.PinState=GPIO_PIN_SET
PB7.Signal=GPIO_Output
PC0.GPIOParameters=GPIO_Label
PC0.GPIO_Label=VSENSE_C
PC0.Mode=IN6-Single-Ended
PC0.Signal=ADC1_IN6
PC1.Signal=SharedAnalog_PC1
PC10.GPIOParameters=GPIO_Label
PC10.GPIO_Label=ENC_SCK
PC10.Mode=Full_Duplex_Master
PC10.Signal=SPI3_SCK
PC11.GPIOParameters=GPIO_Label
PC11.GPIO_Label=ENC_MISO
PC11.Mode=Full_Duplex_Master
PC11.Signal=SPI3_MISO
PC12.GPIOParameters=GPIO_Label
PC12.GPIO_Label=ENC_MOSI
PC12.Mode=Full_Duplex_Master
PC12.Signal=SPI3_MOSI
PC13.Mode=PWM Generation1 CH1 CH1N
PC13.Signal=TIM1_CH1N
PC14-OSC32_IN.GPIOParameters=GPIO_Label
PC14-OSC32_IN.GPIO_Label=LED1
PC14-OSC32_IN.Signal=GPIO_Output
PC15-OSC32_OUT.GPIOParameters=GPIO_Label
PC15-OSC32_OUT.GPIO_Label=LED2
PC15-OSC32_OUT.Signal=GPIO_Output
PC2.GPIOParameters=GPIO_Label
PC2.GPIO_Label=VBUS_SENSE
PC2.Mode=IN8-Single-Ended
PC2.Signal=ADC1_IN8
PC4.Mode=Asynchronous
PC4.Signal=USART1_TX
PC5.Mode=Asynchronous
PC5.Signal=USART1_RX
PC6.GPIOParameters=GPIO_Speed,PinState,GPIO_Label
PC6.GPIO_Label=DRV_CS
PC6.GPIO_Speed=GPIO_SPEED_FREQ_HIGH
PC6.PinState=GPIO_PIN_SET
PC6.Signal=GPIO_Output
PC7.GPIOParameters=GPIO_Speed,PinState,GPIO_Label
PC7.GPIO_Label=DRV_EN
PC7.GPIO_Speed=GPIO_SPEED_FREQ_HIGH
PC7.PinState=GPIO_PIN_SET
PC7.Signal=GPIO_Output
PC8.GPIOParameters=GPIO_Label
PC8.GPIO_Label=ENC_SCL
PC8.Mode=I2C
PC8.Signal=I2C3_SCL
PC9.GPIOParameters=GPIO_Label
PC9.GPIO_Label=ENC_SDA
PC9.Mode=I2C
PC9.Signal=I2C3_SDA
RCC.HSE_VALUE=8000000
RCC.SYSCLKFreq_VALUE=170000000
RCC.SYSCLKSource=RCC_SYSCLKSOURCE_PLLCLK
board=custom

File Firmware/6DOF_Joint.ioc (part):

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Mcu.Name=STM32G431C(6-8-B)Ux
Mcu.Package=UFQFPN48
Mcu.UserName=STM32G431CBUx
PA0.Mode=IN1-Single-Ended
PA0.Signal=ADC1_IN1
PA1.Mode=IN2-Single-Ended
PA1.Signal=ADC1_IN2
PA10.Signal=S_TIM1_CH3
PA11.Mode=FDCAN_Activate
PA11.Signal=FDCAN1_RX
PA12.Mode=FDCAN_Activate
PA12.Signal=FDCAN1_TX
PA13.Mode=Serial_Wire
PA13.Signal=SYS_JTMS-SWDIO
PA14.Mode=Serial_Wire
PA14.Signal=SYS_JTCK-SWCLK
PA15.GPIOParameters=GPIO_Label
PA15.GPIO_Label=ENC_CS
PA15.Signal=GPIO_Output
PA2.Mode=IN3-Single-Ended
PA2.Signal=ADC1_IN3
PA3.Mode=IN4-Single-Ended
PA3.Signal=ADC1_IN4
PA4.GPIOParameters=GPIO_Label
PA4.GPIO_Label=DRV_CS
PA4.Signal=GPIO_Output
PA5.Mode=Full_Duplex_Master
PA5.Signal=SPI1_SCK
PA6.Mode=Full_Duplex_Master
PA6.Signal=SPI1_MISO
PA7.Mode=Full_Duplex_Master
PA7.Signal=SPI1_MOSI
PA8.Signal=S_TIM1_CH1
PA9.Signal=S_TIM1_CH2
PB0.Mode=PWM Generation2 CH2 CH2N
PB0.Signal=TIM1_CH2N
PB1.Mode=IN12-Single-Ended
PB1.Signal=ADC1_IN12
PB10.Mode=Activate-Break-Input
PB10.Signal=TIM1_BKIN
PB13.Mode=PWM Generation1 CH1 CH1N
PB13.Signal=TIM1_CH1N
PB15.Mode=PWM Generation3 CH3 CH3N
PB15.Signal=TIM1_CH3N
PB2.GPIOParameters=GPIO_Label
PB2.GPIO_Label=DRV_EN
PB2.Signal=GPIO_Output
PB5.Mode=Full_Duplex_Master
PB5.Signal=SPI3_MOSI
PB6.Mode=Asynchronous
PB6.Signal=USART1_TX
PB7.Mode=Asynchronous
PB7.Signal=USART1_RX
PC10.Mode=Full_Duplex_Master
PC10.Signal=SPI3_SCK
PC11.Mode=Full_Duplex_Master
PC11.Signal=SPI3_MISO
PC13.GPIOParameters=GPIO_Label
PC13.GPIO_Label=CONNECT_STATE
PC13.Signal=GPIO_Output
PC14-OSC32_IN.Signal=GPIO_Output
PC15-OSC32_OUT.GPIOParameters=GPIO_Label
PC15-OSC32_OUT.GPIO_Label=RUN_STATE
PC15-OSC32_OUT.Signal=GPIO_Output
PF0-OSC_IN.Mode=HSE-External-Oscillator
PF0-OSC_IN.Signal=RCC_OSC_IN
PF1-OSC_OUT.Mode=HSE-External-Oscillator
PF1-OSC_OUT.Signal=RCC_OSC_OUT
RCC.SYSCLKFreq_VALUE=170000000
RCC.SYSCLKSource=RCC_SYSCLKSOURCE_PLLCLK
board=custom
